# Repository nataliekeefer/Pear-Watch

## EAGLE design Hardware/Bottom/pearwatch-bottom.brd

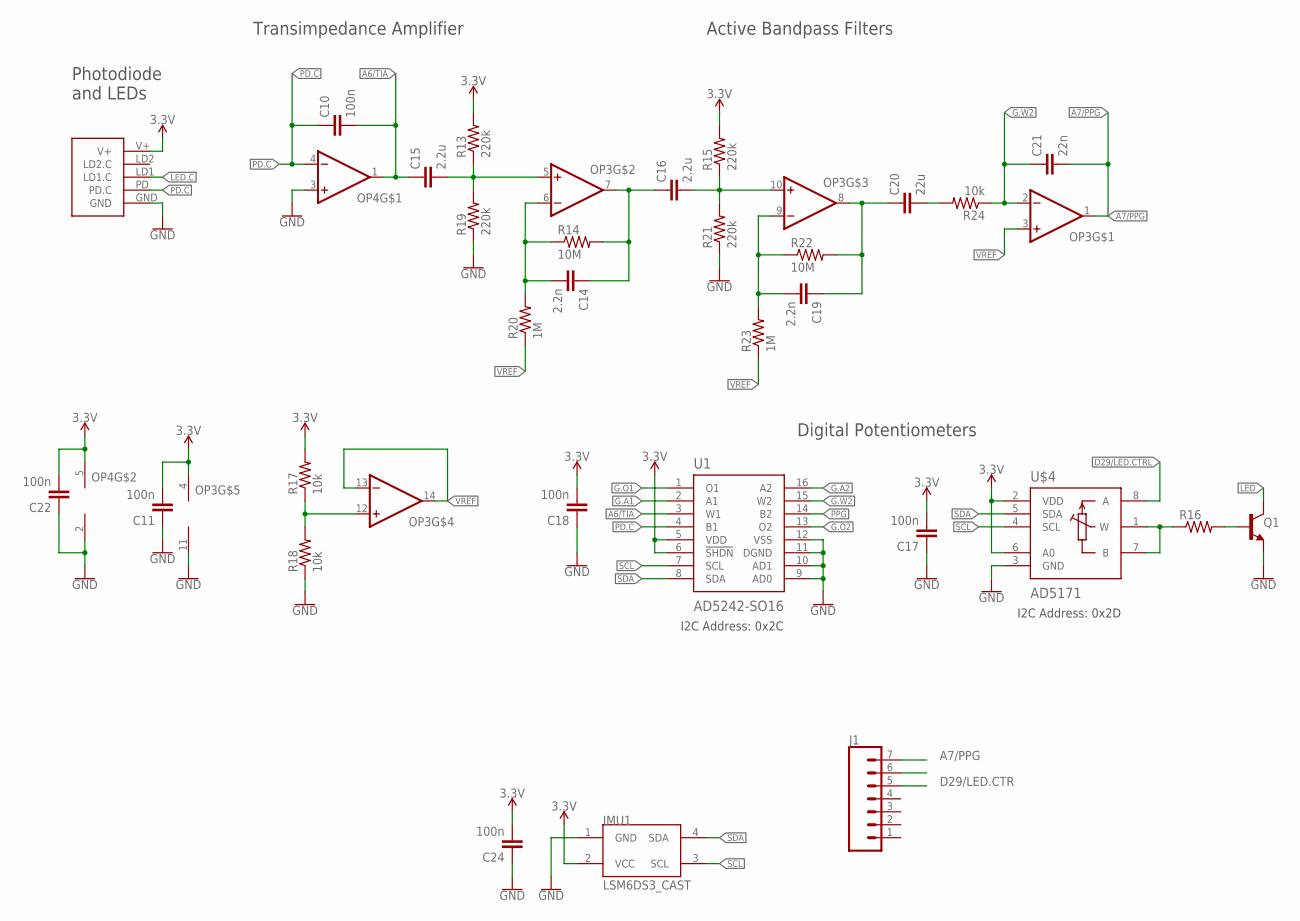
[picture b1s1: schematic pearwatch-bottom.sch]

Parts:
C10, C11, C17, C18, C22, C24: 100n; C0603
C14, C19: 2.2n; C0603
C15, C16: 2.2u; C0603
C20: 22u; C0603
C21: 22n; C0603
IMU1: LSM6DS3_CAST
J1: CONN_07; 1X07
OP3: OP-QUAD-SO14; SO14
OP4: OP-SINGLEOT; SOT23-5
Q1: NPN-GENERIC; SOT23-3
R13, R15, R19, R21: 220k; R0603
R14, R22: 10M; R0603
R16: RESISTOR0603; R0603
R17, R18: 10k; R0402
R20, R23: 1M; R0603
R24: 10k; R0603
U1: AD5242-SO16; SO16
U$3: PPG.MODULE.2
U$4: AD5171; SOT-23-8

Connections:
3.3V: C11.2, C17.2, C18.2, C22.2, C24.2, IMU1.2 (VCC), OP3.4 (V+), OP4.5 (V+), R13.2, R15.2, R17.2, U1.5 (VDD), U1.6 (!SHDN), U$3.V+, U$4.2 (VDD), U$4.6 (A0)
A6/TIA: C10.2, C15.1, J1.5, OP4.1 (OUT), U1.3 (W1)
A7/PPG: C21.2, J1.7, OP3.1 (OUT)
D29/LED.CTR: J1.6
D29/LED.CTRL: U$4.8 (A)
G.A1: U1.2 (A1)
G.A2: U1.16 (A2)
G.O1: U1.1 (O1)
G.O2: U1.13 (O2)
G.W2: C21.1, OP3.2 (-IN), R24.1, U1.15 (W2)
GND: C11.1, C17.1, C18.1, C22.1, C24.1, IMU1.1 (GND), OP3.11 (V-), OP4.2 (V-), OP4.3 (+IN), Q1.2 (E), R18.1, R19.1, R21.1, U1.9 (AD0), U1.10 (AD1), U1.11 (DGND), U1.12 (VSS), U$3.GND, U$4.3 (GND)
LED: Q1.3 (C)
LED.C: U$3.LD1 (LD1.C)
unnamed: Q1.1 (B), R16.2
unnamed: R16.1, U$4.1 (W), U$4.7 (B)
unnamed: OP3.12 (+IN), R17.1, R18.2
unnamed: C15.2, OP3.5 (+IN), R13.1, R19.2
unnamed: C14.2, OP3.6 (-IN), R14.1, R20.2
unnamed: C14.1, C16.1, OP3.7 (OUT), R14.2
unnamed: C16.2, OP3.10 (+IN), R15.1, R21.2
unnamed: C19.2, OP3.9 (-IN), R22.1, R23.2
unnamed: C19.1, C20.1, OP3.8 (OUT), R22.2
unnamed: C20.2, R24.2
PD.C: C10.1, OP4.4 (-IN), U1.4 (B1), U$3.PD (PD.C)
PPG: U1.14 (B2)
SCL: IMU1.3 (SCL), U1.7 (SCL), U$4.4 (SCL)
SDA: IMU1.4 (SDA), U1.8 (SDA), U$4.5 (SDA)
VREF: OP3.3 (+IN), OP3.13 (-IN), OP3.14 (OUT), R20.1, R23.1

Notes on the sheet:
Photodiode and LEDs
Active Bandpass Filters
Digital Potentiometers
Transimpedance Amplifier
I2C Address: 0x2C
I2C Address: 0x2D

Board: 2 copper layers, 32 parts (0 on the bottom side), 19 nets, no tracks yet.

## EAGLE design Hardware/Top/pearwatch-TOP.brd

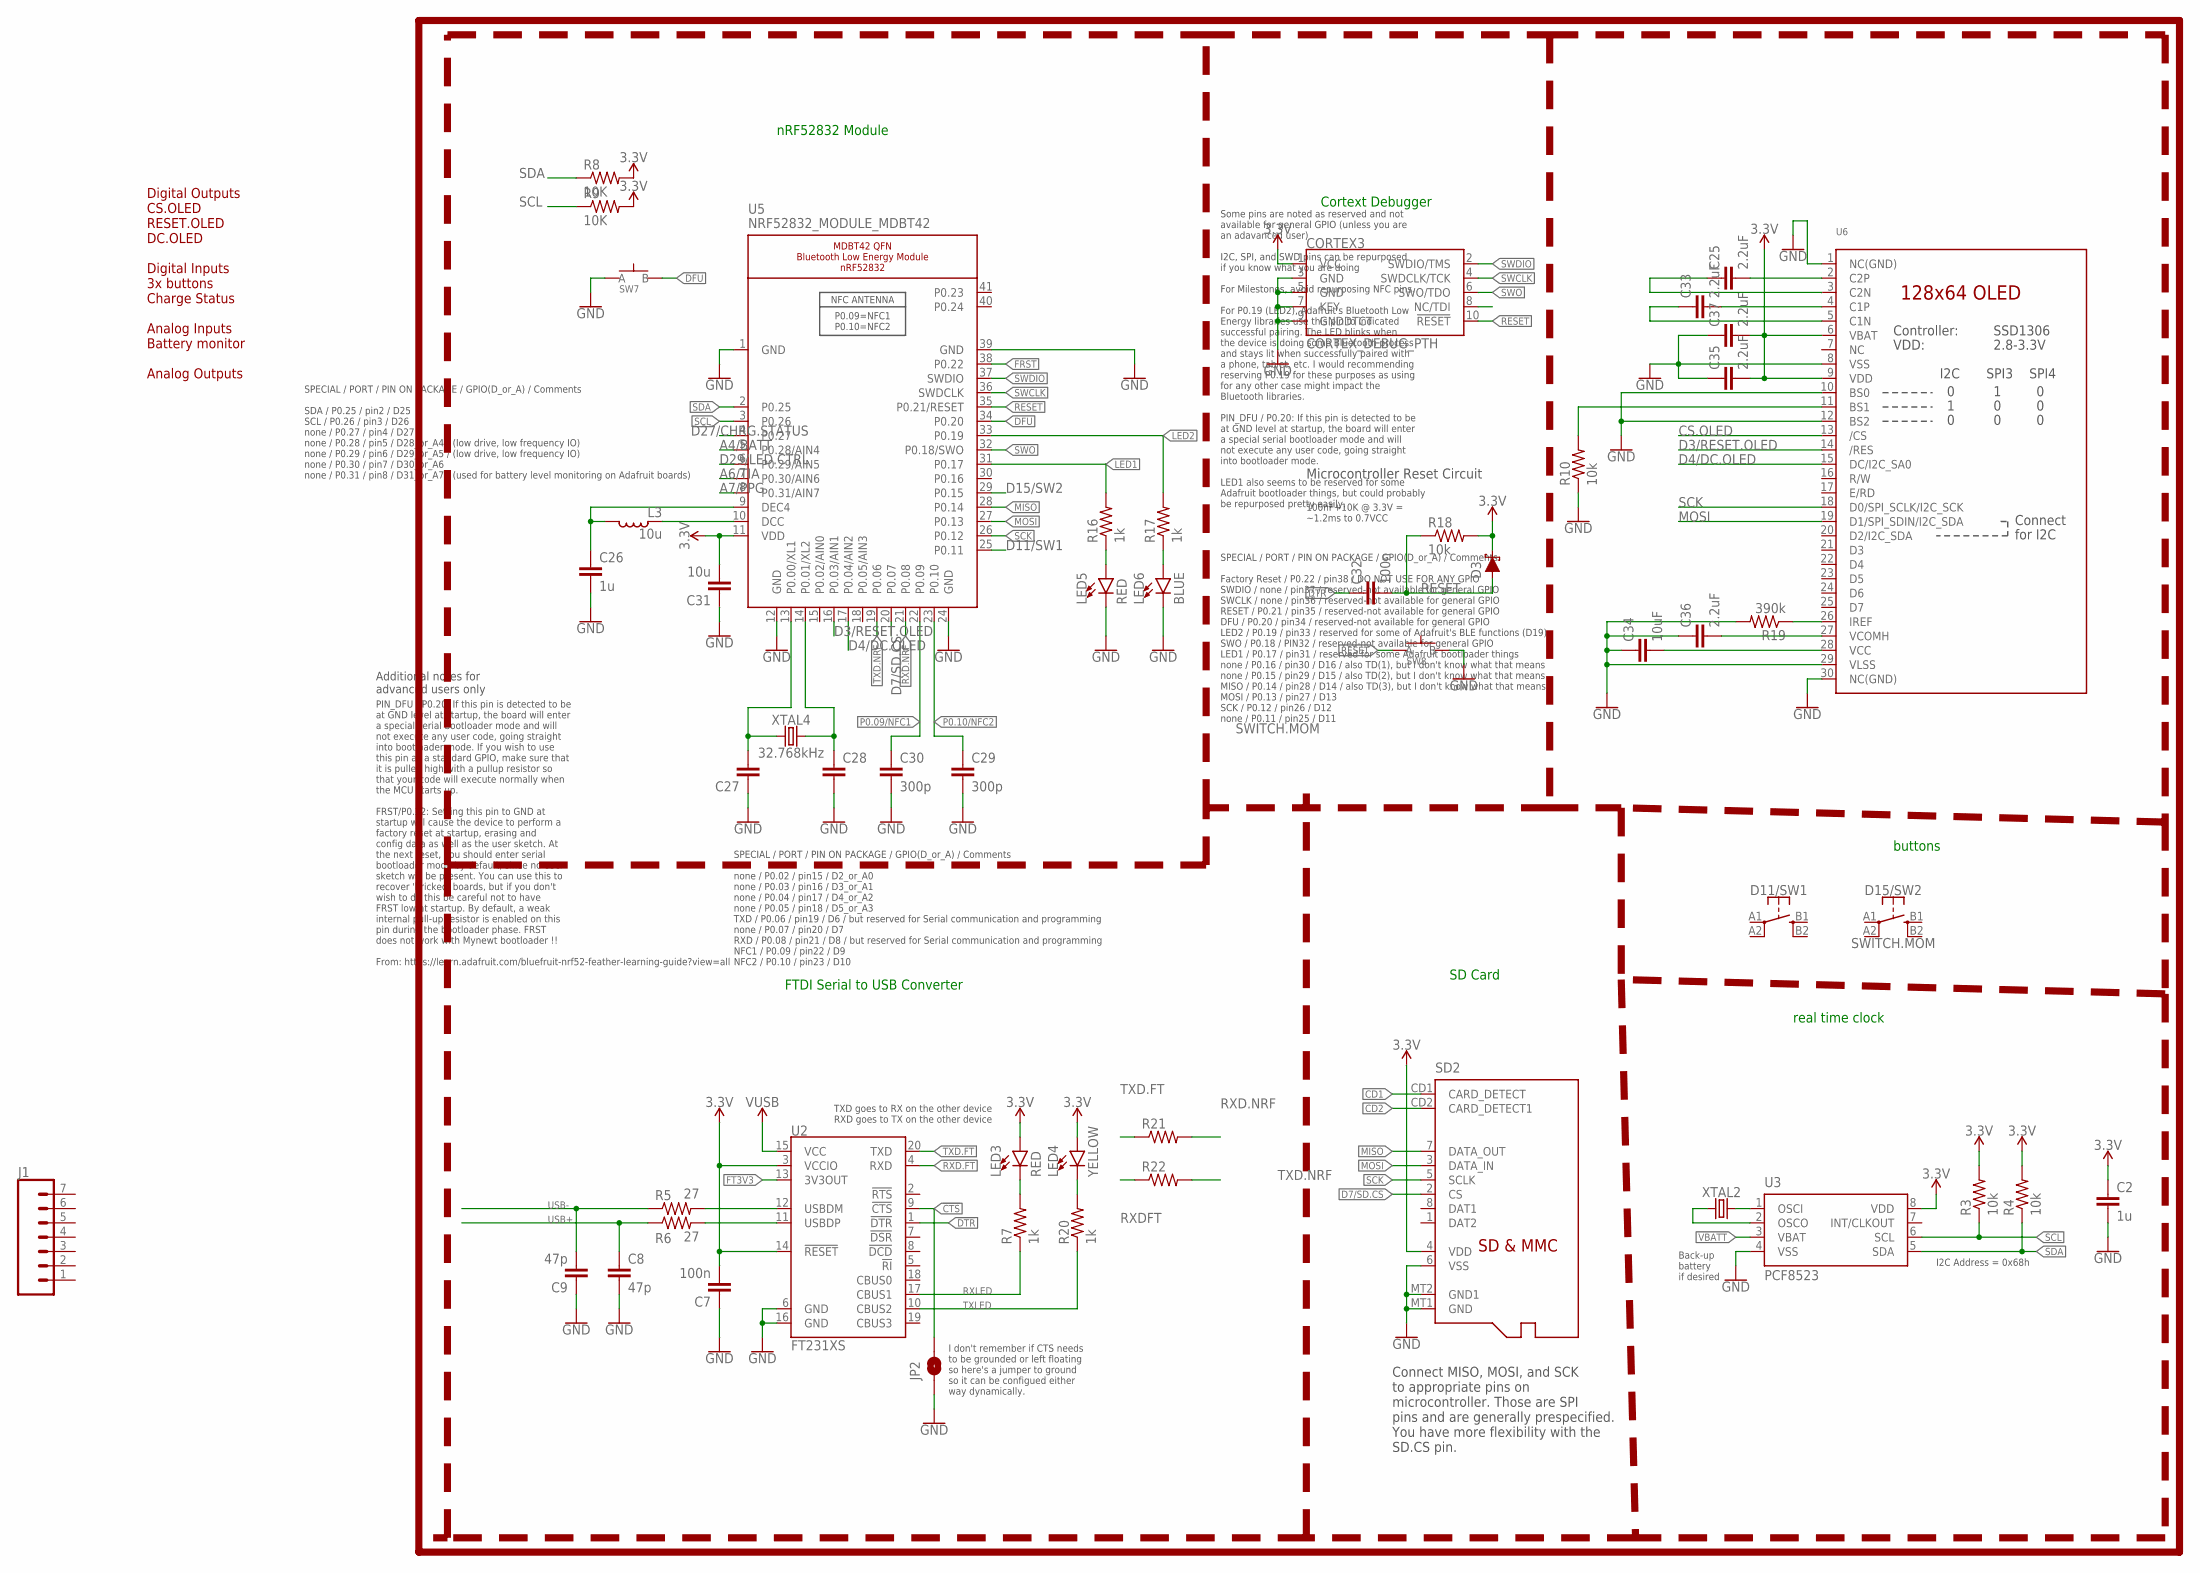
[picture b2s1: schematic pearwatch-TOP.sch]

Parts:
C2, C26: 1u; C0603
C7, C32: 100n; C0603
C8, C9: 47p; C0603
C25, C33, C35, C36, C37: 2.2uF; C0402
C27, C28: CAPACITOR0603; C0603
C29, C30: 300p; C0603
C31: 10u; C0805
C34: 10uF; C0603
CORTEX3: CORTEX_DEBUG_PTH; 2X5-PTH-1.27MM
D3: SCHOTTKY-USC; USC
D11/SW1, D15/SW2: SWITCH.MOM; TACTILE_SWITCH_SMD_6.2MM_TALL
J1: CONN_07; 1X07
JP2: JUMPER-SMT_2_NO_SILK; SMT-JUMPER_2_NO_SILK
L3: 10u; L0603
LED3, LED5: RED; LED-0603
LED4: YELLOW; LED-0603
LED6: BLUE; LED-0603
R3, R4, R10, R18: 10k; R0603
R5, R6: 27; R0603
R7, R16, R17, R20: 1k; R0603
R8, R9: 10K; R0603
R19: 390k; R0603
R21, R22: RESISTOR0603; R0603
SD2: MICROSD
SW7, SW8: SPST-PTS830GG140-COPY.1-3; BUTTON-GULLWING
U2: FT231XS; SSOP20_L
U3: PCF8523; SO8; DIGIKEY 568-5306-1-ND
U5: NRF52832_MODULE_MDBT42; BLE_MODULE_RAYTAC_MDBT42
U6: DISP_OLED_UG-2864HSWEG01-NO-WRAPAROUND; UG-2864HSWEG01_0.96IN_NO-WRAPAROUND
XTAL2: 32.7680kHz; 2-SMD.NOLEAD.2.0MMTO1.2MM
XTAL4: 32.768kHz; 2-SMD.NOLEAD.2.0MMTO1.2MM

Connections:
3.3V: C2.1, C7.2, C31.2, C35.2, C37.2, CORTEX3.1 (VCC), D3.- (C), LED3.A, LED4.A, R3.2, R4.2, R8.2, R9.2, R18.2, SD2.4 (VDD), U2.3 (VCCIO), U2.14 (!RESET), U3.8 (VDD), U5.11 (VDD), U6.6 (VBAT), U6.9 (VDD)
!CTS: JP2.2, U2.9 (!CTS)
!DTR: U2.1 (!DTR)
A4/BATT: U5.5 (P0.28/AIN4)
A6/TIA: U5.7 (P0.30/AIN6)
A7/PPG: U5.8 (P0.31/AIN7)
CD1: SD2.CD1 (CARD_DETECT)
CD2: SD2.CD2 (CARD_DETECT1)
CS.OLED: U6.13 (/CS)
D3/RESET.OLED: U5.16 (P0.03/AIN1), U6.14 (/RES)
D4/DC.OLED: U5.17 (P0.04/AIN2), U6.15 (DC/I2C_SA0)
D7/SD.CS: SD2.2 (CS), U5.20 (P0.07)
D11/SW1: U5.25 (P0.11)
D15/SW2: U5.29 (P0.15)
D27/CHRG.STATUS: U5.4 (P0.27)
D29/LED.CTRL: U5.6 (P0.29/AIN5)
DFU: SW7.3 (B), U5.34 (P0.20)
DTR: C32.1
FRST: U5.38 (P0.22)
FT3V3: U2.13 (3V3OUT)
GND: C2.2, C7.1, C8.2, C9.1, C26.2, C27.1, C28.2, C29.2, C30.2, C31.1, C34.1, C35.1, C36.1, C37.1, CORTEX3.3 (GND), CORTEX3.5 (GND), CORTEX3.7 (KEY), CORTEX3.9 (GNDDTCT), JP2.1, LED5.C, LED6.C, R10.1, R19.2, SD2.6 (VSS), SD2.MT1 (GND), SD2.MT2 (GND1), SW7.1 (A), SW8.3 (B), U2.6 (GND), U2.16 (GND), U3.4 (VSS), U5.1 (GND), U5.12 (GND), U5.24 (GND), U5.39 (GND), U6.1 (NC(GND)), U6.8 (VSS), U6.10 (BS0), U6.12 (BS2), U6.29 (VLSS), U6.30 (NC(GND))
LED1: R16.2, U5.31 (P0.17)
LED2: R17.2, U5.33 (P0.19)
MISO: SD2.7 (DATA_OUT), U5.28 (P0.14)
MOSI: SD2.3 (DATA_IN), U5.27 (P0.13), U6.19 (D1/SPI_SDIN/I2C_SDA)
unnamed: U3.2 (OSCO), XTAL2.P$1 (1)
unnamed: U3.1 (OSCI), XTAL2.P$2 (2)
unnamed: R5.2, U2.12 (USBDM)
unnamed: R6.2, U2.11 (USBDP)
unnamed: LED3.C, R7.2
unnamed: LED4.C, R20.2
unnamed: R10.2, U6.11 (BS1)
unnamed: R19.1, U6.26 (IREF)
unnamed: C25.2, U6.2 (C2P)
unnamed: C27.2, U5.13 (P0.00/XL1), XTAL4.P$1 (1)
unnamed: C28.1, U5.14 (P0.01/XL2), XTAL4.P$2 (2)
unnamed: LED5.A, R16.1
unnamed: LED6.A, R17.1
unnamed: L3.1, U5.10 (DCC)
unnamed: C26.1, L3.2, U5.9 (DEC4)
unnamed: C25.1, U6.3 (C2N)
unnamed: C33.2, U6.4 (C1P)
unnamed: C33.1, U6.5 (C1N)
unnamed: C34.2, U6.28 (VCC)
unnamed: C36.2, U6.27 (VCOMH)
P0.09/NFC1: C30.1, U5.22 (P0.09)
P0.10/NFC2: C29.1, U5.23 (P0.10)
RESET: C32.2, CORTEX3.10 (!RESET), D3.+ (A), R18.1, SW8.1 (A), U5.35 (P0.21/RESET)
RXD.FT: U2.4 (RXD)
RXD.NRF: R21.2, U5.21 (P0.08)
RXDFT: R22.1
RXLED: R7.1, U2.17 (CBUS1)
SCK: SD2.5 (SCLK), U5.26 (P0.12), U6.18 (D0/SPI_SCLK/I2C_SCK)
SCL: R3.1, R9.1, U3.6 (SCL), U5.3 (P0.26)
SDA: R4.1, R8.1, U3.5 (SDA), U5.2 (P0.25)
SWCLK: CORTEX3.4 (SWDCLK/TCK), U5.36 (SWDCLK)
SWDIO: CORTEX3.2 (SWDIO/TMS), U5.37 (SWDIO)
SWO: CORTEX3.6 (SWO/TDO), U5.32 (P0.18/SWO)
TXD.FT: R21.1, U2.20 (TXD)
TXD.NRF: R22.2, U5.19 (P0.06)
TXLED: R20.1, U2.10 (CBUS2)
USB+: C8.1, R6.1
USB-: C9.2, R5.1
VBATT: U3.3 (VBAT)
V_USB: U2.15 (VCC)

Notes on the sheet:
Connect MISO, MOSI, and SCK to appropriate pins on microcontroller. Those are SPI pins and are generally prespecified. You have more flexibility with the SD.CS pin.
buttons
FTDI Serial to USB Converter
SD Card
nRF52832 Module
real time clock
Cortext Debugger
Digital Outputs CS.OLED RESET.OLED DC.OLED Digital Inputs 3x buttons Charge Status Analog Inputs Battery monitor Analog Outputs
Microcontroller Reset Circuit
100nF+10K @ 3.3V = ~1.2ms to 0.7VCC
SPECIAL / PORT / PIN ON PACKAGE / GPIO(D_or_A) / Comments SDA / P0.25 / pin2 / D25 SCL / P0.26 / pin3 / D26 none / P0.27 / pin4 / D27 none / P0.28 / pin5 / D28_or_A4 / (low drive, low frequency IO) none / P0.29 / pin6 / D29_or_A5 / (low drive, low frequency IO) none / P0.30 / pin7 / D30_or_A6 none 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
SPECIAL / PORT / PIN ON PACKAGE / GPIO(D_or_A) / Comments none / P0.02 / pin15 / D2_or_A0 none / P0.03 / pin16 / D3_or_A1 none / P0.04 / pin17 / D4_or_A2 none / P0.05 / pin18 / D5_or_A3 TXD / P0.06 / pin19 / D6 / but reserved for Serial communication and programming none / P0.07 / pin20 / D7 RXD / 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
SPECIAL / PORT / PIN ON PACKAGE / GPIO(D_or_A) / Comments Factory Reset / P0.22 / pin38 / DO NOT USE FOR ANY GPIO SWDIO / none / pin37 / reserved-not available for general GPIO SWCLK / none / pin36 / reserved-not available for general GPIO RESET / P0.21 / pin35 / reserved-not available for general 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
Some pins are noted as reserved and not available for general GPIO (unless you are an adavanced user) I2C, SPI, and SWD pins can be repurposed if you know what you are doing For Milestones, avoid repurposing NFC pins. For P0.19 (LED2), Adafruit's Bluetooth Low Energy libraries use this pin to indic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
PIN_DFU / P0.20: If this pin is detected to be at GND level at startup, the board will enter a special serial bootloader mode and will not execute any user code, going straight into bootloader mode. If you wish to use this pin as a standard GPIO, make sure that it is pulled high with a pullup resis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
Additional notes for advanced users only
TXD goes to RX on the other device RXD goes to TX on the other device
I don't remember if CTS needs to be grounded or left floating so here's a jumper to ground so it can be configued either way dynamically.
I2C Address = 0x68h
Back-up battery if desired

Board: 2 copper layers, 52 parts (1 on the bottom side), 47 nets, no tracks yet.

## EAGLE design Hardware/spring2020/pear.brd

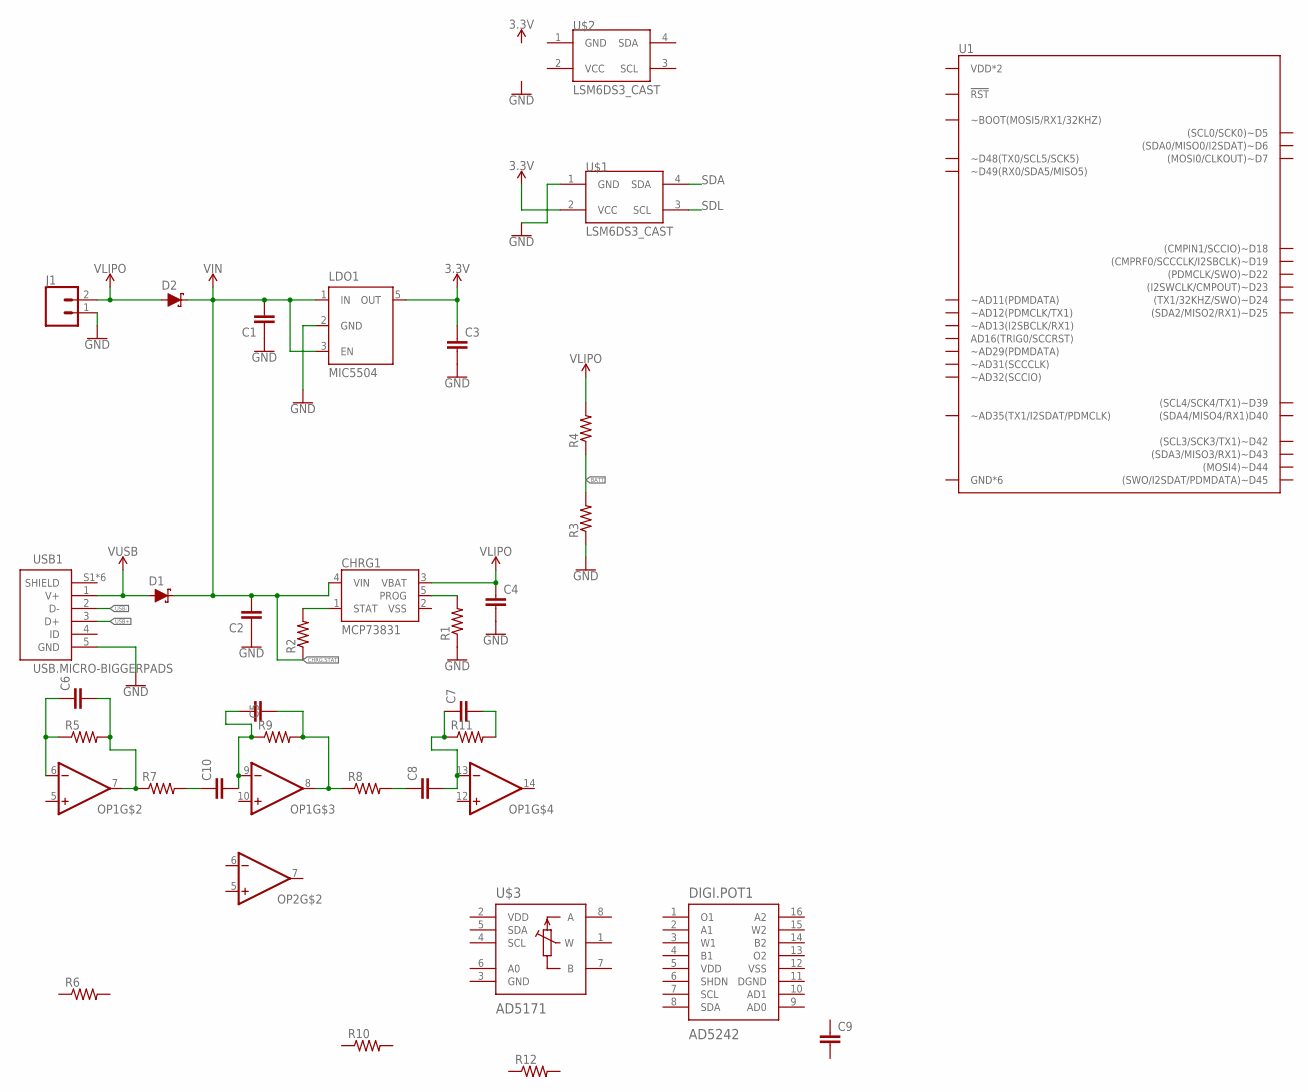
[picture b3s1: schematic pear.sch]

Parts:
C1, C2, C3, C4, C5, C6, C7, C8, C9, C10: CAPACITOR0603; C0603
CHRG1: MCP73831; SOT23-5
D1, D2: SCHOTTKY-USC; USC
DIGI.POT1: AD5242; TSSOP16
J1: CONN_02; 1X02
LDO1: MIC5504; SOT23-5
OP1, OP2: OP-QUAD-SO14; SO14
R1, R2, R3, R4, R5, R6, R7, R8, R9, R10, R11, R12: RESISTOR0603; R0603
U1: ARTEMIS.CAST; ARTEMIS_CAST
U$1, U$2: LSM6DS3_CAST
U$3: AD5171; SOT-23-8
USB1: USB.MICRO-BIGGERPADS; USB-MICRO-01.BIGGERPADS

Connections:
3.3V: C3.1, LDO1.5 (OUT), U$1.2 (VCC)
BATT: R3.2, R4.1
CHRG.STAT: C1.2, C2.2, CHRG1.4 (VIN), D1.- (C), D2.- (C), LDO1.1 (IN), LDO1.3 (EN), R2.1
GND: C1.1, C2.1, C3.2, C4.2, J1.1, LDO1.2 (GND), R1.1, R3.1, U$1.1 (GND), USB1.5 (GND)
unnamed: C10.1, R7.2
unnamed: C6.1, OP1.6 (-IN), R5.1
unnamed: C6.2, OP1.7 (OUT), R5.2, R7.1
unnamed: C5.1, C10.2, OP1.9 (-IN), R9.1
unnamed: C5.2, OP1.8 (OUT), R8.1, R9.2
unnamed: C8.1, R8.2
unnamed: CHRG1.1 (STAT), R2.2
unnamed: C7.1, C8.2, OP1.13 (-IN), R11.1
unnamed: CHRG1.5 (PROG), R1.2
unnamed: C7.2, R11.2
SDA: U$1.4 (SDA)
SDL: U$1.3 (SCL)
USB+: USB1.3 (D+)
USB-: USB1.2 (D-)
V+: OP1.4 (V+), OP2.4 (V+)
V-: OP1.11 (V-), OP2.11 (V-)
VLIPO: C4.1, CHRG1.3 (VBAT), D2.+ (A), J1.2, R4.2
VSS: CHRG1.2 (VSS)
V_USB: D1.+ (A), USB1.1 (V+)

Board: 2 copper layers, 35 parts (0 on the bottom side), 18 nets, no tracks yet.

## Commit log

2020-02-02 my attempt at pushing my first hardware and firmware
2020-05-28 device name
2020-06-03 first 11 minutes of top layer
2020-06-04 organizing
2020-06-04 adding txt file
2020-06-04 adding BOM
2020-06-25 adding updated top board
2020-06-25 adding bottom board
2020-06-25 updating top board
2020-06-25 deleted power management from top board
2020-06-25 making connections top and bottom board
